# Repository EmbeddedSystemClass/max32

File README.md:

# max32
Hardware and Software replacement for MAX! radiator thermostat

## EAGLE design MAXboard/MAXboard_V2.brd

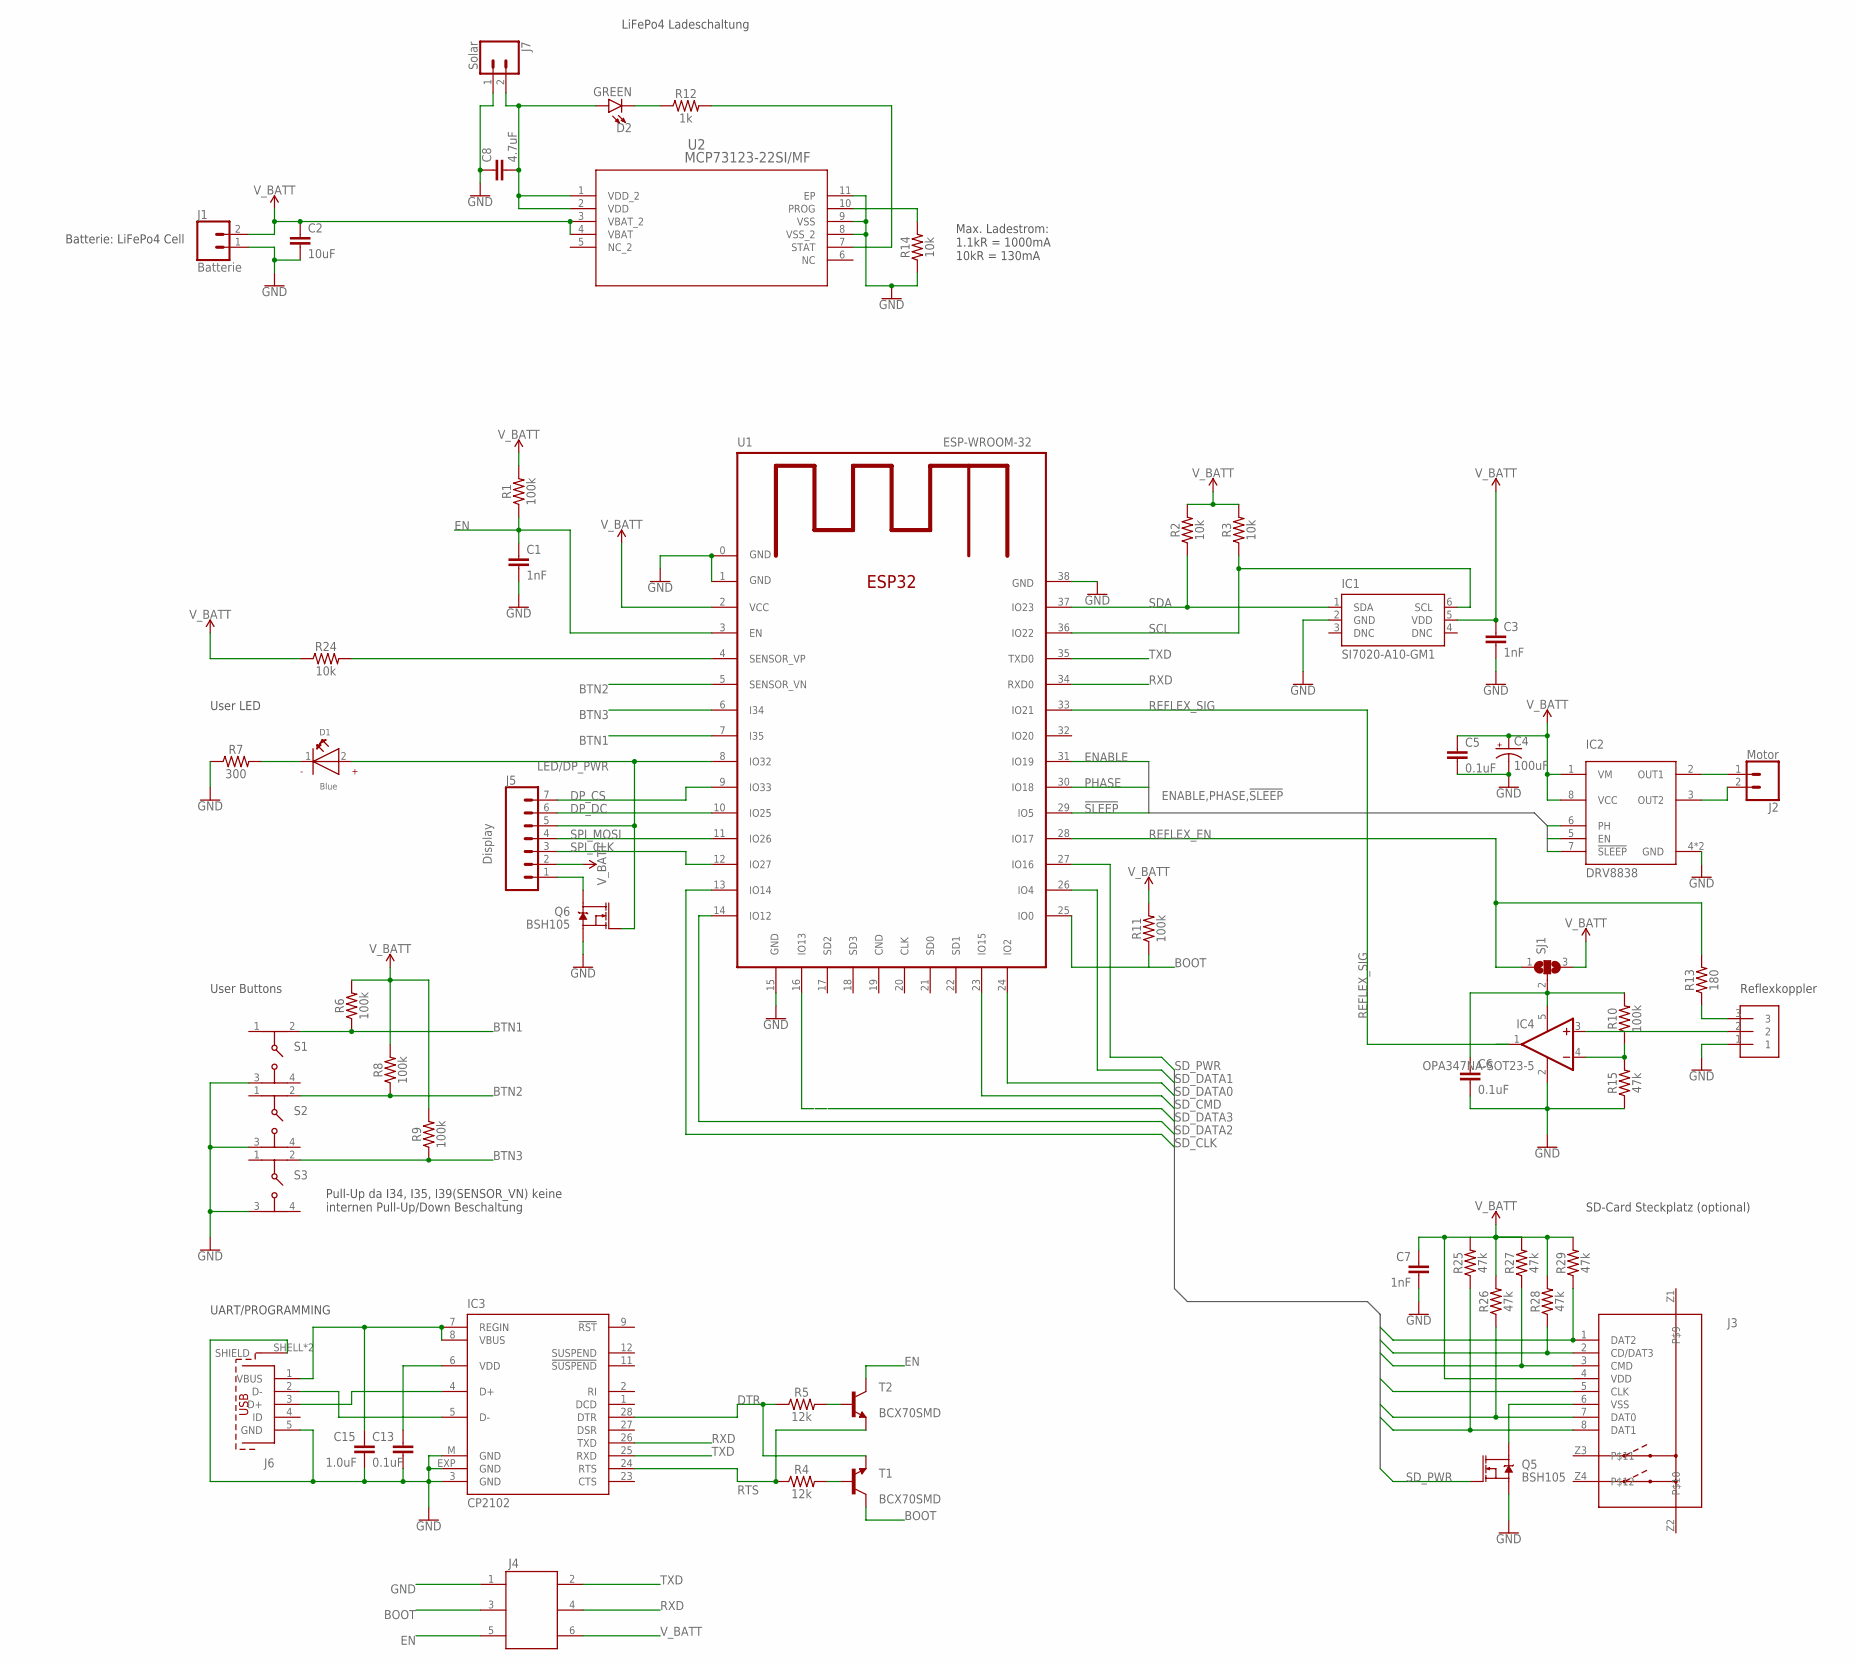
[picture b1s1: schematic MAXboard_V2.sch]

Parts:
C1, C3, C7: 1nF; 0603
C2: 10uF; 0603
C4: 100uF; PANASONIC_D
C5, C6, C13: 0.1uF; 0603
C8: 4.7uF; 0603
C15: 1.0uF; 0603
D1: Blue; WL-SMCW_0603
D2: GREEN; LED-0603
IC1: SI7020-A10-GM1; DFN6-3X3
IC2: DRV8838; WSON8-2X2
IC3: CP2102; MLP28
IC4: OPA347NA-SOT23-5; SOT23-5
J1: Batterie; 1X02
J2: Motor; 1X02
J3: 693072010801
J4: 490107670612
J5: Display; 1X07
J6: 614105150721
J7: Solar; 1X02
Q5, Q6: BSH105; SOT23-3
R1, R6, R8, R9, R10, R11: 100k; 0603
R2, R3, R14, R24: 10k; 0603
R4, R5: 12k; 0603
R7: 300; 0603
R12: 1k; 0603
R13: 180; 0603
R15, R25, R26, R27, R28, R29: 47k; 0603
S1, S2, S3: 430181038816
SJ1: SJ2W; SJ_2
T1, T2: BCX70SMD; SOT23
U1: ESP-WROOM-32; ESP32MOD
U2: MCP73123-22SI/MF; DFN10_3X3MC
U$1: SMD_3; SMD_3X1.28

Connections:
!SLEEP: IC2.7 (!SLEEP), U1.29 (IO5)
BOOT: J4.3, R11.1, T1.3 (C), U1.25 (IO0)
BTN1: R6.1, S1.2 (3), U1.7 (I35)
BTN2: R8.1, S2.2 (3), U1.5 (SENSOR_VN)
BTN3: R9.1, S3.2 (3), U1.6 (I34)
DP_CS: J5.7, U1.9 (IO33)
DP_DC: J5.6, U1.10 (IO25)
DTR: IC3.28 (DTR), R5.1, T1.2 (E)
EN: C1.1, J4.5, R1.1, T2.3 (C), U1.3 (EN)
ENABLE: IC2.5 (EN), U1.31 (IO19)
GND: C1.2, C2.2, C3.2, C4.-, C5.2, C6.2, C7.2, C8.1, C13.2, C15.2, IC1.2 (GND), IC2.4 (GND), IC2.EXP (GND), IC3.3 (GND), IC3.EXP (GND), IC3.M (GND), IC4.2 (V-), J1.1, J4.1, J6.5 (GND), J6.SHELL (SHIELD), J6.SHELL1 (SHIELD), J7.1, Q5.2 (S), Q6.2 (S), R7.1, R14.1, R15.1, S1.3 (2), S2.3 (2), S3.3 (2), U1.0 (GND), U1.1 (GND), U1.15 (GND), U1.38 (GND), U2.8 (VSS_2), U2.9 (VSS), U2.11 (EP), U$1.1
LED/DP_PWR: D1.2 (+), J5.5, Q6.1 (G), U1.8 (IO32)
unnamed: IC4.3 (+IN), U$1.2
unnamed: IC2.2 (OUT1), J2.1
unnamed: IC2.3 (OUT2), J2.2
unnamed: R24.2, U1.4 (SENSOR_VP)
unnamed: D1.1 (-), R7.2
unnamed: R13.1, U$1.3
unnamed: C15.1, IC3.7 (REGIN), IC3.8 (VBUS), J6.1 (VBUS)
unnamed: IC3.5 (D-), J6.2 (D-)
unnamed: IC3.4 (D+), J6.3 (D+)
unnamed: J5.1, Q6.3 (D)
unnamed: C8.2, D2.A, J7.2, U2.1 (VDD_2), U2.2 (VDD)
unnamed: D2.C, R12.1
unnamed: R12.2, U2.7 (STAT)
unnamed: R14.2, U2.10 (PROG)
unnamed: J3.6 (VSS), Q5.3 (D)
unnamed: IC4.4 (-IN), R10.1, R15.2
unnamed: C6.1, IC4.5 (V+), R10.2, SJ1.2
unnamed: R4.2, T1.1 (B)
unnamed: R5.2, T2.1 (B)
unnamed: C13.1, IC3.6 (VDD)
PHASE: IC2.6 (PH), U1.30 (IO18)
REFLEX_EN: R13.2, SJ1.1, U1.28 (IO17)
REFLEX_SIG: IC4.1 (OUT), U1.33 (IO21)
RTS: IC3.24 (RTS), R4.1, T2.2 (E)
RXD: IC3.26 (TXD), J4.4, U1.34 (RXD0)
SCL: IC1.6 (SCL), R3.1, U1.36 (IO22)
SDA: IC1.1 (SDA), R2.1, U1.37 (IO23)
SD_CLK: J3.5 (CLK), U1.13 (IO14)
SD_CMD: J3.3 (CMD), R27.1, U1.23 (IO15)
SD_DATA0: J3.7 (DAT0), R26.1, U1.24 (IO2)
SD_DATA1: J3.8 (DAT1), R25.1, U1.26 (IO4)
SD_DATA2: J3.1 (DAT2), R29.1, U1.14 (IO12)
SD_DATA3: J3.2 (CD/DAT3), R28.1
SD_PWR: Q5.1 (G), U1.27 (IO16)
SPI_CLK: J5.3, U1.12 (IO27)
SPI_MOSI: J5.4, U1.11 (IO26)
TXD: IC3.25 (RXD), J4.2, U1.35 (TXD0)
V_BATT: C2.1, C3.1, C4.+, C5.1, C7.1, IC1.5 (VDD), IC2.1 (VM), IC2.8 (VCC), J1.2, J3.4 (VDD), J4.6, J5.2, R1.2, R2.2, R3.2, R6.2, R8.2, R9.2, R11.2, R24.1, R25.2, R26.2, R27.2, R28.2, R29.2, SJ1.3, U1.2 (VCC), U2.3 (VBAT_2), U2.4 (VBAT)

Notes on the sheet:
User LED
SD-Card Steckplatz (optional)
Reflexkoppler
User Buttons
UART/PROGRAMMING
Pull-Up da I34, I35, I39(SENSOR_VN) keine internen Pull-Up/Down Beschaltung
Max. Ladestrom: 1.1kR = 1000mA 10kR = 130mA
LiFePo4 Ladeschaltung
Batterie: LiFePo4 Cell

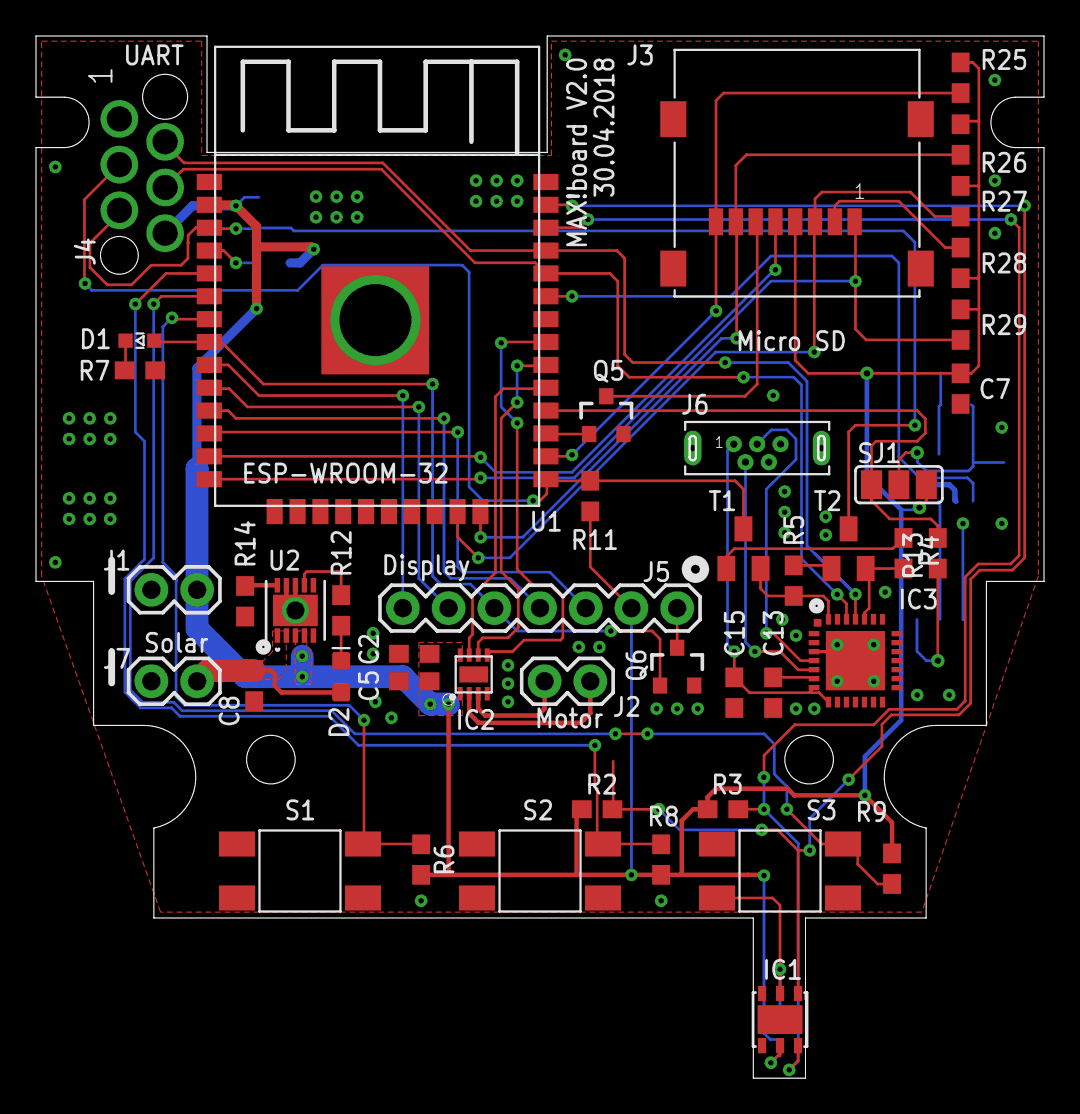
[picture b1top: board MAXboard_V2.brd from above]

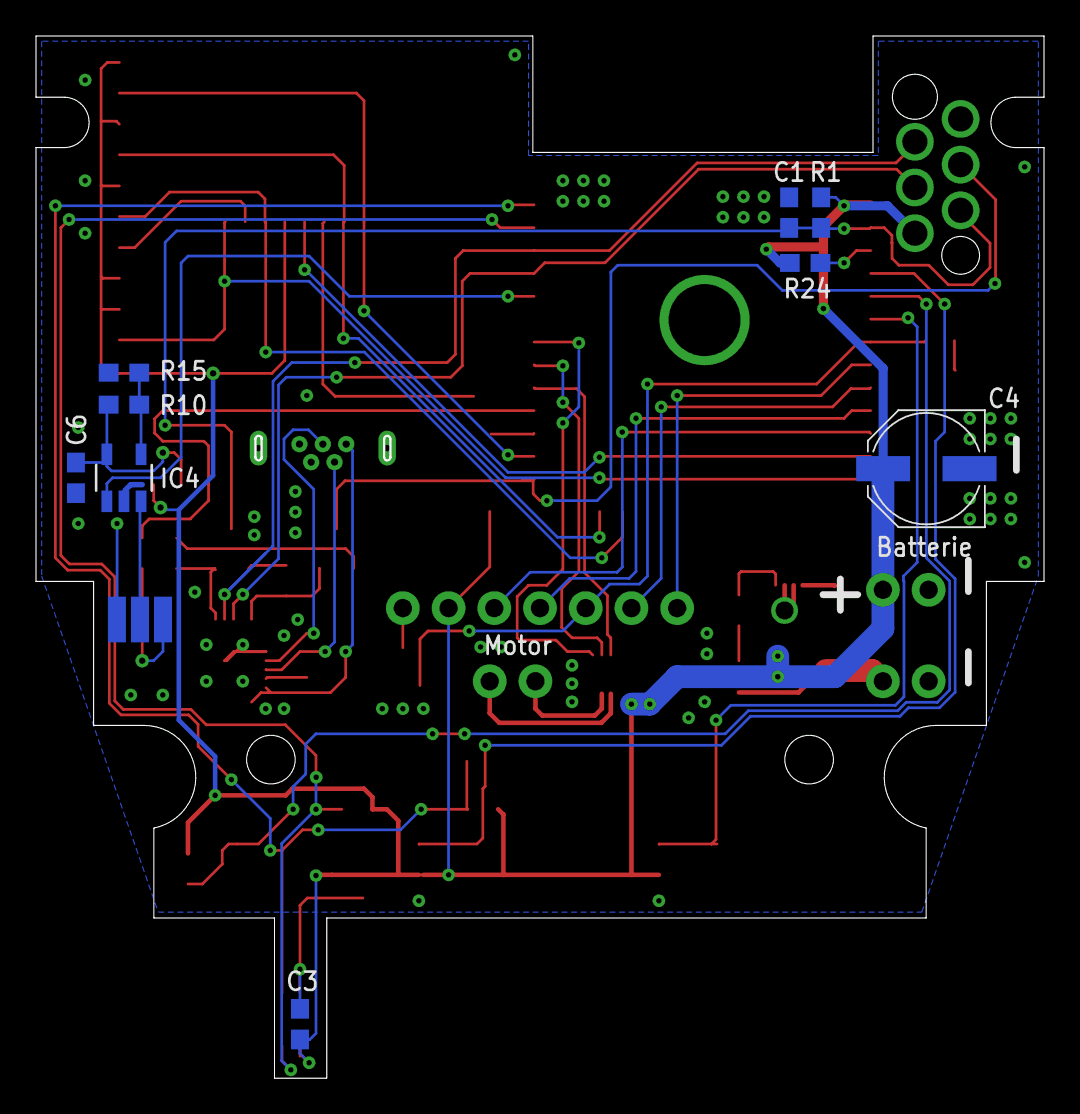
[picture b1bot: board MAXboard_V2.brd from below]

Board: 2 copper layers, 55.9 x 57.8 mm, 55 parts (10 on the bottom side), 50 nets.

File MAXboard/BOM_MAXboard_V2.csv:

"Part";"Value";"Device";"Package";"Description";"COMPANY-URL";"CREATED-BY";"CREATED-DATE";"DATASHEET-URL";"MANUFACTURER";"MANUFACTURER_PART_NUMBER";"MF";"MPN";"OC_FARNELL";"OC_NEWARK";"PROD_ID";"VALUE";"VENDOR";
"C1";"1nF";"1.0NF/1000PF-0603-50V-10%";"0603";"1nF/1,000pF ceramic capacitors";"";"";"";"";"";"";"";"";"";"";"CAP-07886";"1nF";"";
"C2";"10uF";"10UF-0603-6.3V-20%";"0603";"10.0µF ceramic capacitors";"";"";"";"";"";"";"";"";"";"";"CAP-11015";"10uF";"";
"C3";"1nF";"1.0NF/1000PF-0603-50V-10%";"0603";"1nF/1,000pF ceramic capacitors";"";"";"";"";"";"";"";"";"";"";"CAP-07886";"1nF";"";
"C4";"100uF";"100UF-POLAR-25V-20%(ELEC)";"PANASONIC_D";"100µF polarized capacitors";"";"";"";"";"";"";"";"";"";"";"CAP-12547";"100uF";"";
"C5";"0.1uF";"0.1UF-0603-25V-(+80/-20%)";"0603";"0.1µF ceramic capacitors";"";"";"";"";"";"";"";"";"";"";"CAP-00810";"0.1uF";"";
"C7";"1nF";"1.0NF/1000PF-0603-50V-10%";"0603";"1nF/1,000pF ceramic capacitors";"";"";"";"";"";"";"";"";"";"";"CAP-07886";"1nF";"";
"C8";"4.7uF";"4.7UF0603";"0603";"4.7µF ceramic capacitors";"";"";"";"";"";"";"";"";"";"";"CAP-08280";"4.7uF";"";
"C12";"dnp";"1.0NF/1000PF-0603-50V-10%";"0603";"1nF/1,000pF ceramic capacitors";"";"";"";"";"";"";"";"";"";"";"CAP-07886";"1nF";"";
"C13";"0.1uF";"0.1UF-0603-25V-5%";"0603";"0.1µF ceramic capacitors";"";"";"";"";"";"";"";"";"";"";"CAP-08604";"0.1uF";"";
"C15";"1.0uF";"1.0UF-0603-16V-10%";"0603";"1µF ceramic capacitors";"";"";"";"";"";"";"";"";"";"";"CAP-00868";"1.0uF";"";
"D1";"Blue";"WL-SMCW-150060BS75000-B";"WL-SMCW_0603";"SMD mono-color Chip LED";"http://www.we-online.de";"Christin Otto";"APR 2013";"http://katalog.we-online.de/en/led/WL-SMCW?m=t&sq=smcw&sp=&s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";"Würth Elektronik eiSos GmbH";"";"";"";"";"";"";"";"";
"D2";"GREEN";"LED-GREEN0603";"LED-0603";"Green SMD LED";"";"";"";"";"";"";"";"";"";"";"DIO-00821";"GREEN";"";
"IC1";"SI7020-A10-GM1";"SI7020-A10-GM1";"DFN6-3X3";"I2C Humidity and Temperature Sensor";"";"";"";"";"";"";"Silicon Labs";"Si7020-GM1";"2422565";"55X3108";"";"";"";
"IC2";"DRV8838";"DRV8838";"WSON8-2X2";"";"";"";"";"";"";"";"";"";"";"";"";"";"";
"IC3";"CP2102";"CP2102";"MLP28";"Single-Chip USB to UART Bridge";"";"";"";"";"";"";"FARNELL";"CP2102-GM";"9282130";"30K5635";"";"";"";
"J1";"Batterie";"CONN_02";"1X02";"Multi connection point. Often used as Generic Header-pin footprint for 0.1 inch spaced/style header connections";"";"";"";"";"";"";"";"";"";"";"";"";"";
"J2";"Motor";"CONN_02";"1X02";"Multi connection point. Often used as Generic Header-pin footprint for 0.1 inch spaced/style header connections";"";"";"";"";"";"";"";"";"";"";"";"";"";
"J3";"";"693072010801";"693072010801";"WR-CRD MICRO SD CARD CONNECTOR HINGE 8PINS=>Code : Con_I-O_COM_CRD_SD_Micro_696072010801";"";"";"";"";"";"";"";"";"";"";"";"";"";
"J4";"";"490107670612";"490107670612";"WR-WST REDFIT IDC, 6 Pins";"";"";"";"";"";"";"";"";"";"";"";"";"";
"J5";"Display";"CONN_07";"1X07";"Multi connection point. Often used as Generic Header-pin footprint for 0.1 inch spaced/style header connections";"";"";"";"";"";"";"";"";"";"";"";"";"";
"J6";"";"614105150721";"614105150721";"WR-COM_USB_Micro Type B_Vertical_THT;";"";"";"";"";"";"";"";"";"";"";"";"";"";
"J7";"Solar";"CONN_02";"1X02";"Multi connection point. Often used as Generic Header-pin footprint for 0.1 inch spaced/style header connections";"";"";"";"";"";"";"";"";"";"";"";"";"";
"Q5";"BSH105";"MOSFET-NCH-AO3404A";"SOT23-3";"N-channel MOSFETs";"";"";"";"";"";"";"";"";"";"";"TRANS-12988";"5.8A/30V/35mO";"";
"Q6";"BSH105";"MOSFET-NCH-AO3404A";"SOT23-3";"N-channel MOSFETs";"";"";"";"";"";"";"";"";"";"";"TRANS-12988";"5.8A/30V/35mO";"";
"R1";"100k";"100KOHM-0603-1/10W-1%";"0603";"100kO resistor";"";"";"";"";"";"";"";"";"";"";"RES-07828";"100k";"";
"R2";"10k";"10KOHM-0603-1/10W-1%";"0603";"10kO resistor";"";"";"";"";"";"";"";"";"";"";"RES-00824";"10k";"";
"R3";"10k";"10KOHM-0603-1/10W-1%";"0603";"10kO resistor";"";"";"";"";"";"";"";"";"";"";"RES-00824";"10k";"";
"R4";"12k";"12KOHM-0603-1/10W-1%";"0603";"12kO resistor";"";"";"";"";"";"";"";"";"";"";"RES-10327";"12k";"";
"R5";"12k";"12KOHM-0603-1/10W-1%";"0603";"12kO resistor";"";"";"";"";"";"";"";"";"";"";"RES-10327";"12k";"";
"R6";"100k";"100KOHM-0603-1/10W-1%";"0603";"100kO resistor";"";"";"";"";"";"";"";"";"";"";"RES-07828";"100k";"";
"R7";"300";"300OHM-0603-1/10W-1%";"0603";"300O resistor";"";"";"";"";"";"";"";"";"";"";"RES_10328";"300";"";
"R8";"100k";"100KOHM-0603-1/10W-1%";"0603";"100kO resistor";"";"";"";"";"";"";"";"";"";"";"RES-07828";"100k";"";
"R9";"100k";"100KOHM-0603-1/10W-1%";"0603";"100kO resistor";"";"";"";"";"";"";"";"";"";"";"RES-07828";"100k";"";
"R10";"0";"10OHM-0603-1/10W-1%";"0603";"10O resistor";"";"";"";"";"";"";"";"";"";"";"RES-12581";"10";"";
"R11";"100k";"100KOHM-0603-1/10W-1%";"0603";"100kO resistor";"";"";"";"";"";"";"";"";"";"";"RES-07828";"100k";"";
"R12";"1k";"1KOHM-0603-1/10W-1%";"0603";"1kO resistor";"";"";"";"";"";"";"";"";"";"";"RES-07856";"1k";"";
"R13";"180";"10OHM-0603-1/10W-1%";"0603";"10O resistor";"";"";"";"";"";"";"";"";"";"";"RES-12581";"10";"";
"R14";"10k";"10KOHM-0603-1/10W-1%";"0603";"10kO resistor";"";"";"";"";"";"";"";"";"";"";"RES-00824";"10k";"";
"R24";"10k";"10KOHM-0603-1/10W-1%";"0603";"10kO resistor";"";"";"";"";"";"";"";"";"";"";"RES-00824";"10k";"";
"R25";"47k";"47KOHM-0603-1/10W-1%";"0603";"47kO resistor";"";"";"";"";"";"";"";"";"";"";"RES-07871";"47k";"";
"R26";"47k";"47KOHM-0603-1/10W-1%";"0603";"47kO resistor";"";"";"";"";"";"";"";"";"";"";"RES-07871";"47k";"";
"R27";"47k";"47KOHM-0603-1/10W-1%";"0603";"47kO resistor";"";"";"";"";"";"";"";"";"";"";"RES-07871";"47k";"";
"R28";"47k";"47KOHM-0603-1/10W-1%";"0603";"47kO resistor";"";"";"";"";"";"";"";"";"";"";"RES-07871";"47k";"";
"R29";"47k";"47KOHM-0603-1/10W-1%";"0603";"47kO resistor";"";"";"";"";"";"";"";"";"";"";"RES-07871";"47k";"";
"S1";"";"430181038816";"430181038816";"4.5x4.5 mm SMD WS-TASV";"";"";"";"";"";"";"";"";"";"";"";"";"";
"S2";"";"430181038816";"430181038816";"4.5x4.5 mm SMD WS-TASV";"";"";"";"";"";"";"";"";"";"";"";"";"";
"S3";"";"430181038816";"430181038816";"4.5x4.5 mm SMD WS-TASV";"";"";"";"";"";"";"";"";"";"";"";"";"";
"T1";"BCX70SMD";"BCX70SMD";"SOT23";"NPN TRANSISTOR";"";"";"";"";"";"";"";"";"";"";"";"";"";
"T2";"BCX70SMD";"BCX70SMD";"SOT23";"NPN TRANSISTOR";"";"";"";"";"";"";"";"";"";"";"";"";"";
"U$1";"SMD_3";"SMD_3";"SMD_3X1.28";"";"";"";"";"";"";"";"";"";"";"";"";"";"";
"U1";"ESP-WROOM-32";"ESP32MOD";"ESP32MOD";"ESP32 Module";"";"";"";"";"";"";"";"";"";"";"";"";"";
"U2";"MCP73123-22SI/MF";"MCP73123-22SI/MF";"DFN10_3X3MC";"";"";"";"";"";"";"MCP7312322SIMF";"";"";"";"";"";"";"Microchip";

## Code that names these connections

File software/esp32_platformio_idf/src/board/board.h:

#ifndef BOARD_H
#define BOARD_H

#include "driver/gpio.h"
#include "driver/i2c.h"
#include "driver/spi_master.h"
#include "driver/uart.h"

#define BOARD_VERSION 2
#define BOARD_MAJOR_VERSION 2
#define BOARD_MINOR_VERSION 0

// SD Card
#define SD_POWER  16
#define SD_CLK    14
#define SD_CMD    15
#define SD_DATA0  2
#define SD_DATA1  4
#define SD_DATA2  12
#define SD_DATA3  13

//Refelx photocell/Rotary encoder
#define REFLEX_EN   17
#define REFLEX_SIG  21

//Motor controller (DRV8838)
#define MOTOR_nSLEEP 5
#define MOTOR_ENABLE 19
#define MOTOR_PHASE  18

//Temperature and humidity sensor (SI7020)
#define SENS_SDA  23
#define SENS_SCL  22

//UART
#define UART_TX 1
#define UART_RX 3

/* Peripheral defines */
//Temperature and humidity sensot (SI7020)
#define SI7020_ADDR 0x40

/* Macros */
#define DELAY_MS(m) ((m/portTICK_RATE_MS))

#if BOARD_VERSION == 1

/* PINMAP 
PIN(CHIP)  FUNCTION     PERIPHERIE    DESCRIPTION
6  (I34)   Digital IN   Button 3
7  (I35)   Digital IN   Button 1
8  (IO32)  Digital OUT  LED Red
9  (IO33)  Digital IN   Button 2
10 (IO25)  Digital OUT  LED Green
11 (IO26)  -            -
12 (IO27)  -            -
13 (IO14)  SD_CLK       SD Card Clock
14 (IO12)  SD_DATA2     SD Card Data#2
16 (IO13)  SD_DATA3     SD Card Data#3
17 (SD2)   DP_DC        Display Data/Command
18 (SD3)   DP_RST       Display Reset
19 (CMD)   SPI_CS       Display SPI Chipselect
20 (CLK)   SPI_CLK      Display SPI Clock
21 (SD0)   SPI_MOSI     Display SPI MOSI
22 (SD1)   -            -
23 (IO15)  SD_CMD       SD Card Command
24 (IO2)   SD_DATA0     SD Card Data#0
25 (IO25)  BOOT         -
26 (IO4)   SD_DATA1     SD Card Data#1
27 (IO16)  Digital OUT  LED Blue/SD Card Power
28 (IO17)  Digital OUT  Reflex Enable (REFLEX_EN)
29 (IO5)   Digital OUT  Motor nSleep
30 (IO18)  Digital OUT  Motor Phase
31 (IO19)  Digital OUT  Motor Enable
32 (IO20)  -            - 
33 (IO21) Digital IN    Reflex Signal (REFLEX_SIG)
34 (RXD0) RXD           UART Receive
35 (TXD0) TXD           UART Transmit
36 (IO22) SCL           SI7020 I²C Clock
37 (IO23) SDA           SI7020 I²C Data
*/

/* Hardware defines */
//Leds
#define LED_RED   32
#define LED_GREEN 25 //LED_GRREN shares pin with display on/off signal
#define LED_BLUE  16 //LED_BLUE shares pin with SD on/off signal

//Userbuttons
#define BUTTON_1  35
#define BUTTON_2  33
#define BUTTON_3  34

//Display
#define DISP_POWER 25 //LED_GRREN shares pin with display on/off signal
#define DISP_DC    9
#define DISP_RST   10
#define SPI_CS     11
#define SPI_CLK    6
#define SPI_MOSI   7

void board_setLedRed(bool state);
void board_setLedGreen(bool state);
void board_setLedBlue(bool state);

//Compatibility wrapper
#define board_setLed(b) (board_setLedRed(b))

#endif

#if BOARD_VERSION == 2

/* PINMAP 
PIN(CHIP)  FUNCTION     PERIPHERIE    DESCRIPTION
4  (I36)   Analog IN    Battery       Batter voltage measurement
5  (I39)   Digital IN   Button 2
6  (I34)   Digital IN   Button 3
7  (I35)   Digital IN   Button 1
8  (IO32)  Digital OUT  User LED & Display Power
9  (IO33)  Digital OUT  Display SPI Chipselect
10 (IO25)  Digital OUT  Display SPI Data/Command
11 (IO26)  SPI_MOSI     Display SPI MOSI
12 (IO27)  SPI_CLK      Display SPI Clock
13 (IO14)  SD_CLK       SD Card Clock
14 (IO12)  SD_DATA2     SD Card Data#2
16 (IO13)  SD_DATA3     SD Card Data#3
17 (SD2)   DP_DC        Display Data/Command
18 (SD3)   DP_RST       Display Reset
19 (CMD)   -            -
20 (CLK)   -            -
21 (SD0)   -            -
22 (SD1)   -            -
23 (IO15)  SD_CMD       SD Card Command
24 (IO2)   SD_DATA0     SD Card Data#0
25 (IO25)  BOOT         -
26 (IO4)   SD_DATA1     SD Card Data#1
27 (IO16)  Digital OUT  SD Card Power (SD_POWER)
28 (IO17)  Digital OUT  Reflex Enable (REFLEX_EN)
29 (IO5)   Digital OUT  Motor nSleep
30 (IO18)  Digital OUT  Motor Phase
31 (IO19)  Digital OUT  Motor Enable
32 (IO20)  -            - 
33 (IO21) Digital IN    Reflex Signal (REFLEX_SIG)
34 (RXD0) RXD           UART Receive
35 (TXD0) TXD           UART Transmit
36 (IO22) SCL           SI7020 I²C Clock
37 (IO23) SDA           SI7020 I²C Data
*/

/* Hardware defines */
//Leds
#define LED       32

//Userbuttons
#define BUTTON_1  35
#define BUTTON_2  39
#define BUTTON_3  34

//Display
#define DISP_POWER 32 //Shared with LED
#define DISP_DC    25
#define SPI_CS     33
#define SPI_CLK    27
#define SPI_MOSI   26

#endif

#ifdef __cplusplus
extern "C" {
#endif

/* Global interface instances */

//Temperature and Humidity Sensor
extern const i2c_port_t THSPort;

//UART Serial interface
extern const uart_port_t SERIALPort;

/* Prototypes */

//Init all port pins and ports
int board_init(void);

//Setter function for led true = on, false = off
void board_setLed(bool state);

//Setter function for reflex enable pin
void board_setReflexEn(bool state);
//Getter function for reflex enable pin
bool  board_getReflexEn();
//Getter function for refelx input pin
bool board_getReflexSig();

#ifdef __cplusplus
}
#endif

#endif //BOARD_H

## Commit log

2018-07-01 Initial commit for Max!Board V 2.0

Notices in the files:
parts and their libraries:
si70xx-10: (c) 2014 Samuel Lourenço
SparkFun-DiscreteSemi: Licensing: Creative Commons ShareAlike 4.0 International - https://creativecommons.org/licenses/by-sa/4.0
EAGLE-COLOR_LED-rev17a: Copyright: Würth Elektronik
